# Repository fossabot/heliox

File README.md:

# Heliox

Uses: https://github.com/GHOSCHT/simple-electron-react-boilerplate

Dashboard: node-gyp fails on sqlite3 build -> set default pyhton version to python 2
```
node-gyp --python /path/to/python2.7/python.exe
```
or
```
npm config set python /path/to/executable/python2.7
```   

## License

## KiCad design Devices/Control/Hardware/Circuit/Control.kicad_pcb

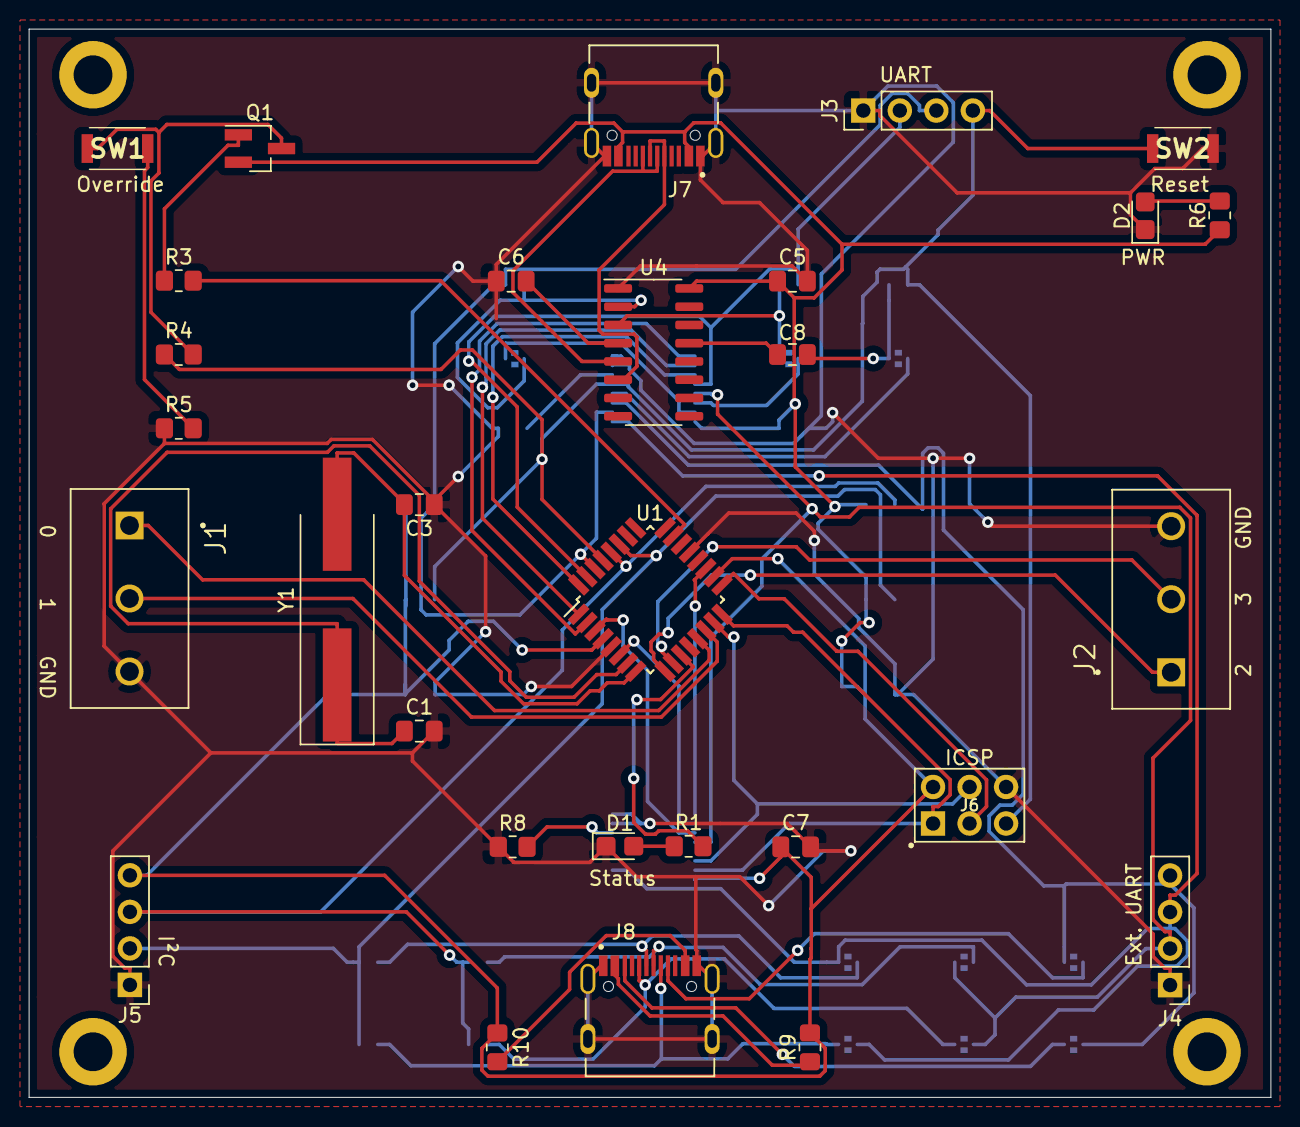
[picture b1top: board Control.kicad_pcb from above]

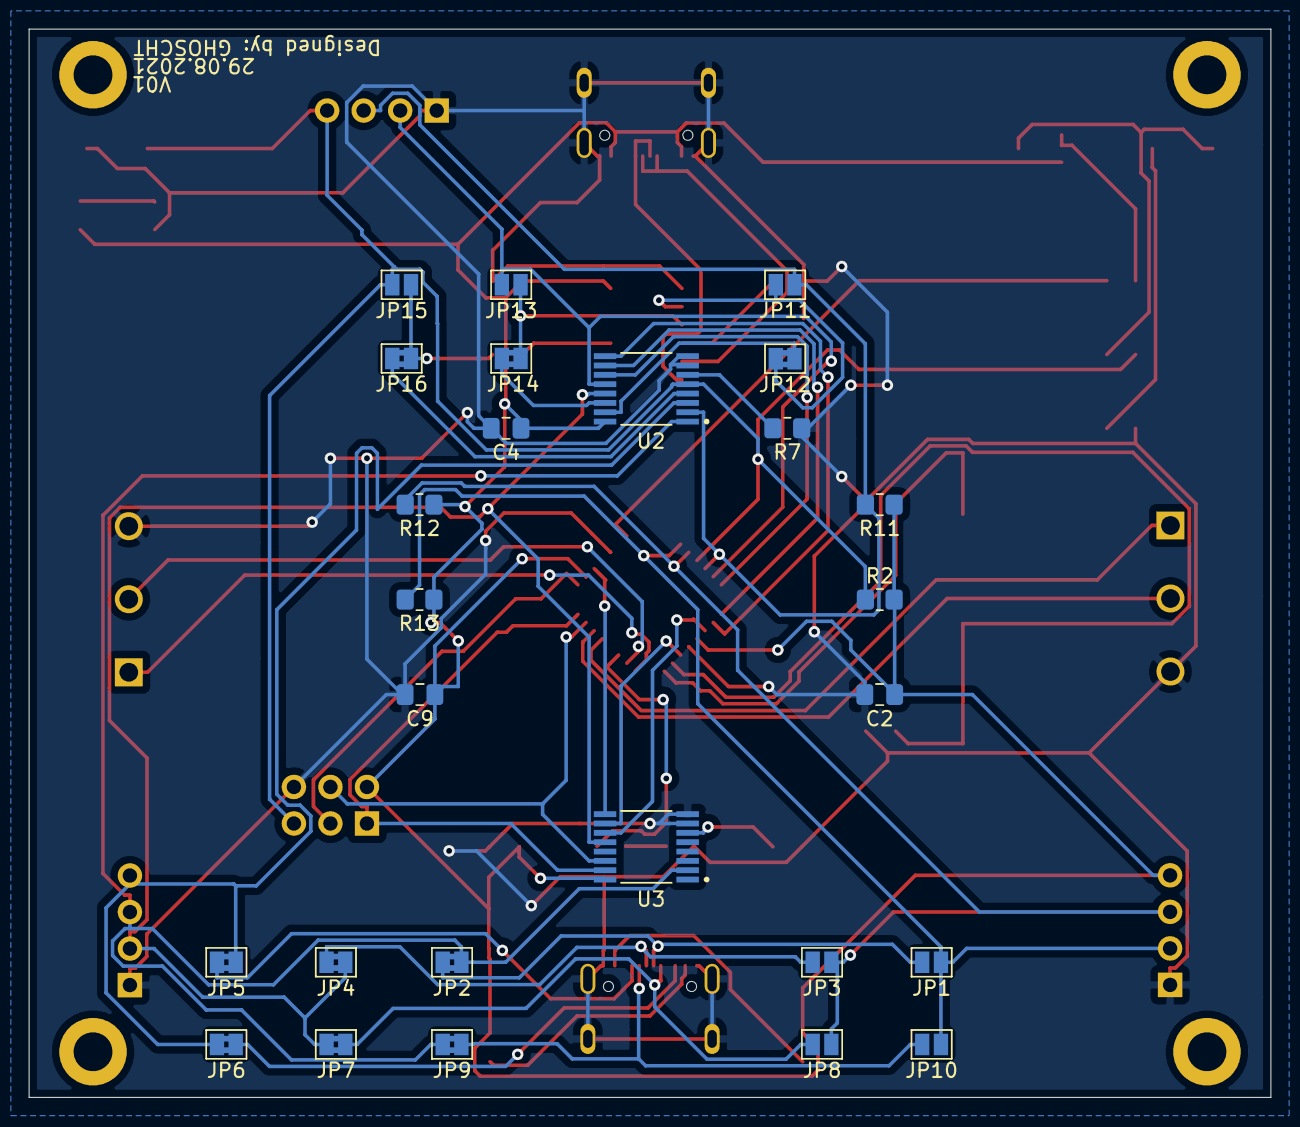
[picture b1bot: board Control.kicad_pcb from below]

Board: 2 copper layers, 86.4 x 74.3 mm, 60 parts (26 on the bottom side), 52 nets.

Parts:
C1, C3: 22p; C_0805_2012Metric_Pad1.18x1.45mm_HandSolder
C2, C4, C5, C6, C7, C8, C9: 100n; C_0805_2012Metric_Pad1.18x1.45mm_HandSolder
D1, D2: 17-21/BHC-XL2M2TY/3T; LED_0805_2012Metric_Castellated
J1, J2: Screw_Terminal_01x03; CUI_TB006-508-03BE
J3, J4, J5: Conn_01x04; PinHeader_1x04_P2.54mm_Vertical
J6: AVR-ISP-6; AVR-ISP
J7, J8: TYPE-C-31-M-12; HRO_TYPE-C-31-M-12
JP1, JP3, JP8, JP10, JP11, JP13, JP15: SolderJumper; SolderJumper-2_P1.3mm_Open_Pad1.0x1.5mm
JP2, JP4, JP5, JP6, JP7, JP9, JP12, JP14, JP16: SolderJumper_Bridged; SolderJumper-2_P1.3mm_Bridged2Bar_Pad1.0x1.5mm
MNT1, MNT2, MNT3, MNT4: MountingHole_2.7mm_M2.5_DIN965_Pad
Q1: Q_NPN_BCE; SOT-23_Handsoldering
R1, R6: 200; R_0805_2012Metric_Pad1.20x1.40mm_HandSolder
R2, R7, R8, R11, R12, R13: 10k; R_0805_2012Metric_Pad1.20x1.40mm_HandSolder
R3, R5, R9, R10: 40.2; R_0805_2012Metric_Pad1.20x1.40mm_HandSolder
R4: 120; R_0805_2012Metric_Pad1.20x1.40mm_HandSolder
SW1, SW2: SW_Push; SKRKAEE020
U1: ATmega328PB-AU; TQFP-32_7x7mm_P0.8mm
U2, U3: CD74HC4053PWR; SOP65P640X120-16N
U4: CH340C; SOIC-16_3.9x9.9mm_P1.27mm
Y1: 16MHz; Crystal_SMD_HC49-SD_HandSoldering

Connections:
D+: J7.A6, J7.B6, U4.5
D-: J7.A7, J7.B7, U4.6
EXTRST: J4.4, JP5.1, JP6.2, U2.3
EXTRX: J4.3, JP2.1, JP9.2, U2.1, U3.2
EXTTX: J4.2, JP4.1, JP7.2, U2.13, U3.12
GND: C1.2, C2.2, C3.2, C4.2, C5.2, C6.1, C7.2, C9.2, D1.1, D2.1, J1.3, J2.3, J3.1, J4.1, J5.1, J6.6, J7.A1B12, J7.B1A12, J7.S1, J7.S2, J7.S3, J7.S4, J8.A1B12, J8.B1A12, J8.S1, J8.S2, J8.S3, J8.S4, R5.1, R7.1, R8.1, SW2.2, U1.5, U1.21, U2.7, U2.8, U3.7, U3.8, U4.1
LED: R1.2, U1.11
MISO: J6.1, U1.16, U3.15
MOSI: J6.4, U1.15, U3.14
MUX1S0: U1.32, U2.11
MUX1S1: U1.1, U2.10
MUX1S2: U1.2, U2.9
MUX2S0: U1.3, U3.11
MUX2S1: U1.6, U3.10
MUX2S2: U1.19, U3.9
MUXRST: JP16.1, U2.4
MUXRX: JP12.1, U2.15
MUXTX: JP14.1, U2.14
unnamed: C6.2, U4.4
unnamed: C8.1, JP15.1, JP16.2
unnamed: C8.2, U4.13
unnamed: D1.2, R1.1
unnamed: D2.2, R6.1
unnamed: J8.A4B9, R9.2
unnamed: J8.A6, JP1.2, JP2.2
unnamed: J8.A7, JP3.2, JP4.2
unnamed: J8.A8, JP5.2
unnamed: J8.B4A9, R10.2
unnamed: J8.B6, JP9.1, JP10.2
unnamed: J8.B7, JP7.1, JP8.2
unnamed: J8.B8, JP6.1
unnamed: JP11.1, JP12.2, U4.2
unnamed: JP13.1, JP14.2, U4.3
unnamed: Q1.1, R3.1
unnamed: Q1.3, R4.2, SW1.1
unnamed: R5.2, SW1.2
unnamed: R7.2, U2.6
unnamed: R8.2, U3.6
RST: J3.4, J6.5, JP15.2, R2.1, R4.1, SW2.1, U1.29, U2.5
RX: J3.3, JP11.2, R11.2, U1.30, U2.2
SCK: J6.3, U1.17
SCL: J5.3, JP3.1, JP8.1, R12.2, U1.28
SDA: J5.2, JP1.1, JP10.1, R13.2, U1.27
SIG1A: J1.1, U1.13
SIG1B: J1.2, U1.14
SIG2A: J2.1, U1.9
SIG2B: J2.2, U1.10
STOPRST: R3.2, U1.23
TX: J3.2, JP13.2, U1.31, U2.12
VCC: C2.1, C4.1, C5.1, C7.1, C9.1, J5.4, J6.2, J7.A4B9, J7.B4A9, Q1.2, R2.2, R6.2, R9.1, R10.1, R11.1, R12.1, R13.1, U1.4, U1.18, U2.16, U3.16, U4.16
XTAL1: C1.1, U1.7, Y1.1
XTAL2: C3.1, U1.8, Y1.2

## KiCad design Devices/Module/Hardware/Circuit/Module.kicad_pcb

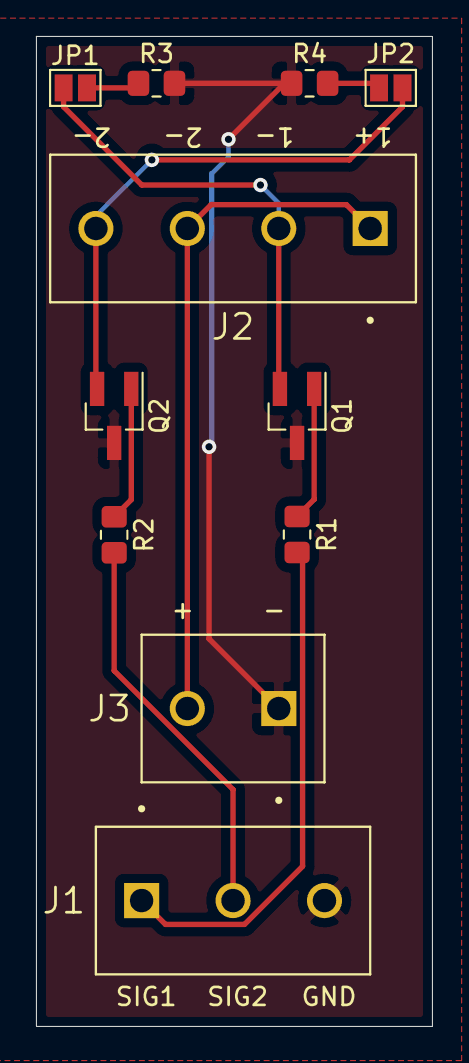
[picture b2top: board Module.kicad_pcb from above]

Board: 2 copper layers, 22.0 x 55.0 mm, 11 parts (0 on the bottom side), 10 nets.

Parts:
J1: Screw_Terminal_01x03; CUI_TB006-508-03BE
J2: Screw_Terminal_01x04; CUI_TB006-508-04BE
J3: Screw_Terminal_01x02; CUI_TB006-508-02BE
JP1, JP2: Jumper; SolderJumper-2_P1.3mm_Open_Pad1.0x1.5mm
Q1, Q2: Q_NPN_BCE; SOT-23_Handsoldering
R1, R2: 470; R_0805_2012Metric_Pad1.20x1.40mm_HandSolder
R3, R4: 10k; R_0805_2012Metric_Pad1.20x1.40mm_HandSolder

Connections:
GND: J1.3, J3.1, Q1.3, Q2.3, R3.2, R4.1
LED1N: J2.2, JP1.1, Q1.2
LED2N: J2.4, JP2.1, Q2.2
unnamed: JP1.2, R3.1
unnamed: JP2.2, R4.2
unnamed: Q1.1, R1.1
unnamed: Q2.1, R2.1
SIG1: J1.1, R1.2
SIG2: J1.2, R2.2
VCC: J2.1, J2.3, J3.2

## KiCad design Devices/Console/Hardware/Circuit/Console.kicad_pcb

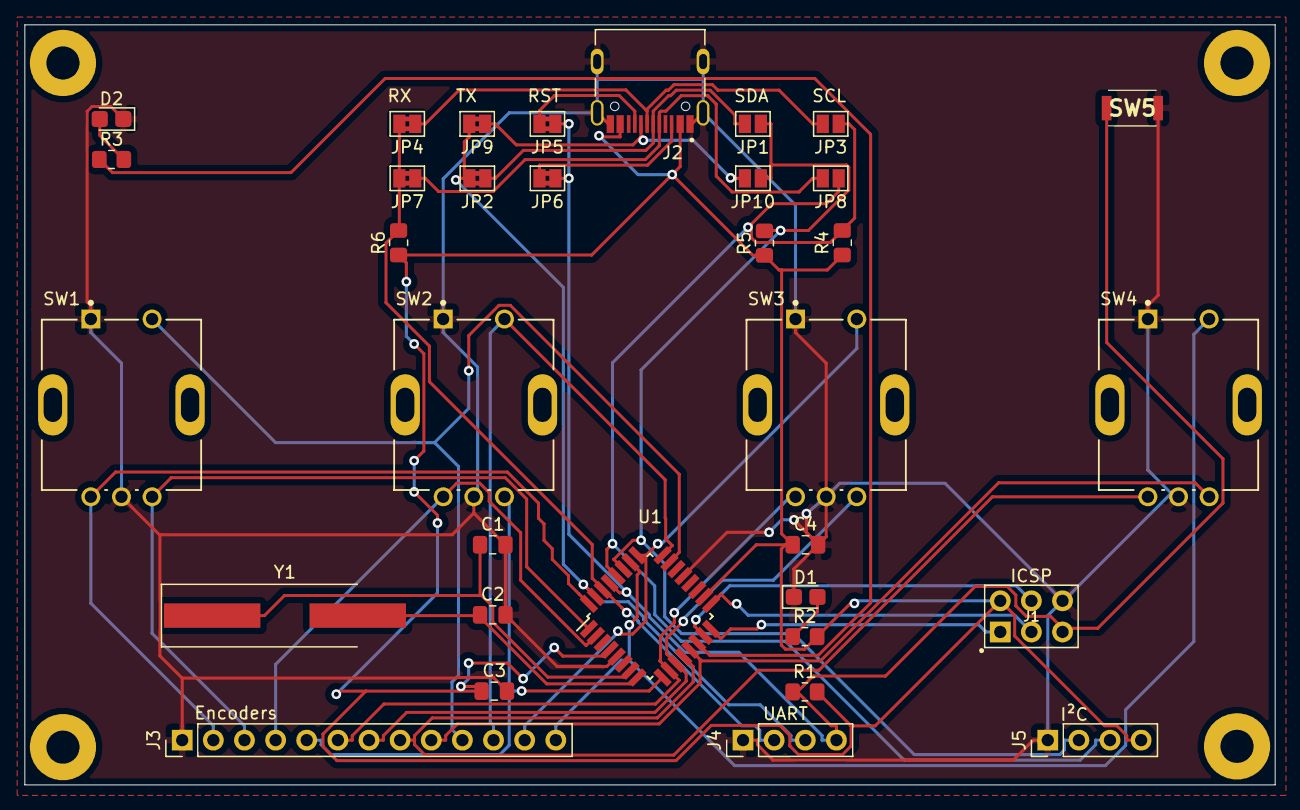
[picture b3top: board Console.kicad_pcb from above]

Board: 2 copper layers, 102.0 x 62.0 mm, 38 parts (0 on the bottom side), 33 nets.

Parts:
C1, C2: 22p; C_0805_2012Metric_Pad1.18x1.45mm_HandSolder
C3, C4: 100n; C_0805_2012Metric_Pad1.18x1.45mm_HandSolder
D1, D2: 17-21/BHC-XL2M2TY/3T; LED_0805_2012Metric_Castellated
J1: AVR-ISP-6; AVR-ISP
J2: TYPE-C-31-M-12; HRO_TYPE-C-31-M-12
J3: Conn_01x13; PinHeader_1x13_P2.54mm_Vertical
J4, J5: Conn_01x04; PinHeader_1x04_P2.54mm_Vertical
JP1, JP3, JP8, JP10: SolderJumper; SolderJumper-2_P1.3mm_Open_Pad1.0x1.5mm
JP2, JP4, JP5, JP6, JP7, JP9: SolderJumper_Bridged; SolderJumper-2_P1.3mm_Bridged2Bar_Pad1.0x1.5mm
PAD1, PAD2, PAD3, PAD4: MountingHole_2.7mm_M2.5_Pad
R1, R4, R5, R6: 10k; R_0805_2012Metric_Pad1.20x1.40mm_HandSolder
R2, R3: 200; R_0805_2012Metric_Pad1.20x1.40mm_HandSolder
SW1, SW2, SW3, SW4: PEC11R-4220F-S0012; Bourns-PEC11R-4220F-S0012-MFG
SW5: SW_Push; SKRKAEE020
U1: ATmega328PB-AU; TQFP-32_7x7mm_P0.8mm
Y1: 16MHz; Crystal_SMD_HC49-SD_HandSoldering

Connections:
BTN1: J3.10, SW1.S2, U1.23
BTN2: J3.11, SW2.S2, U1.24
BTN3: J3.12, SW3.S2, U1.25
BTN4: J3.13, SW4.S2, U1.26
ENC1A: J3.2, SW1.A, U1.32
ENC1B: J3.3, SW1.B, U1.1
ENC2A: J3.4, SW2.A, U1.2
ENC2B: J3.5, SW2.B, U1.9
ENC3A: J3.6, SW3.A, U1.10
ENC3B: J3.7, SW3.B, U1.11
ENC4A: J3.8, SW4.A, U1.12
ENC4B: J3.9, SW4.B, U1.13
GND: C1.2, C2.2, C3.2, C4.2, D1.1, D2.1, J1.6, J2.A1B12, J2.B1A12, J2.S1, J2.S2, J2.S3, J2.S4, J3.1, J4.1, J5.1, SW1.C, SW1.S1, SW2.C, SW2.S1, SW3.C, SW3.S1, SW4.C, SW4.S1, SW5.2, U1.5, U1.21
LED: R3.2, U1.14
MISO: J1.1, U1.16
MOSI: J1.4, U1.15
unnamed: D1.2, R2.1
unnamed: D2.2, R3.1
unnamed: J2.A6, JP1.2, JP2.2
unnamed: J2.A7, JP3.2, JP4.2
unnamed: J2.A8, JP5.2
unnamed: J2.B6, JP9.1, JP10.1
unnamed: J2.B7, JP7.1, JP8.1
unnamed: J2.B8, JP6.1
RST: J1.5, J4.4, JP5.1, JP6.2, R1.1, SW5.1, U1.29
RX: J4.2, JP4.1, JP7.2, R6.2, U1.30
SCK: J1.3, U1.17
SCL: J5.3, JP3.1, JP8.2, R4.2, U1.28
SDA: J5.2, JP1.1, JP10.2, R5.2, U1.27
TX: J4.3, JP2.1, JP9.2, U1.31
VCC: C3.1, C4.1, J1.2, J2.A4B9, J2.B4A9, J5.4, R1.2, R2.2, R4.1, R5.1, R6.1, U1.4, U1.18
XTAL1: C1.1, U1.7, Y1.1
XTAL2: C2.1, U1.8, Y1.2

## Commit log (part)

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2020-07-28 Add Dashboard
2020-07-28 Create LICENSE
2020-07-30 Switch electron boilerplates
2020-07-30 Add on & off commands + Relay state communication
2020-07-30 Add serialport package
2020-07-30 remove menu bar
2020-07-30 first serial com test
2020-08-01 Remove default content
2020-08-01 Add redux store
2020-08-01 Add material ui
2020-08-01 First test of serial control
2020-08-01 Add darkmode
2020-08-01 Change app name
2020-08-01 Add icon, size & name change
2020-08-01 Remove test component
2020-08-01 Add conditional styling
2020-08-01 Remove unnecessary props
2020-08-01 Add hide to tray
2020-08-01 Change icon
2020-08-01 Simplify tray creation
2020-08-01 cleanup
2020-08-01 Add icon to resources
2020-08-01 Add new styling
2020-08-01 No logical changes, only clarification
2020-08-01 Change file format of icon
2020-08-01 Bump mixin-deep from 1.3.1 to 1.3.2 in /Dashboard
    Bumps [mixin-deep](https://github.com/jonschlinkert/mixin-deep) from 1.3.1 to 1.3.2.
    - [Release notes](https://github.com/jonschlinkert/mixin-deep/releases)
    - [Commits](https://github.com/jonschlinkert/mixin-deep/compare/1.3.1...1.3.2)
2020-08-01 Bump electron from 8.2.2 to 8.2.4 in /Dashboard
    Bumps [electron](https://github.com/electron/electron) from 8.2.2 to 8.2.4.
    - [Release notes](https://github.com/electron/electron/releases)
    - [Changelog](https://github.com/electron/electron/blob/master/docs/breaking-changes.md)
    - [Commits](https://github.com/electron/electron/compare/v8.2.2...v8.2.4)
2020-08-01 Bump lodash from 4.17.11 to 4.17.19 in /Dashboard
    Bumps [lodash](https://github.com/lodash/lodash) from 4.17.11 to 4.17.19.
    - [Release notes](https://github.com/lodash/lodash/releases)
    - [Commits](https://github.com/lodash/lodash/compare/4.17.11...4.17.19)
2020-08-02 Disable publishing
2020-08-02 Arduino builder error test
2020-08-02 Revert "Arduino builder error test"
    This reverts commit 97cf7e37e65544a997c7bfe0c96db386e0ee02a5.
2020-08-02 Icon experimentation
2020-08-02 Linting changes
2020-08-05 Add single instance lock
2020-08-07 Hardware config changes
2020-08-07 Comments + minor changes
2020-08-07 Remove quit event
2020-08-07 take trayIcon oncklick event out of creation function
2020-08-07 More comments
2020-08-07 Remove icon2.ico
2020-08-07 Remove unused variable
2020-08-07 Remove winow focussing
2020-08-07 Add devtools shortcut
2020-08-07 Display tray icon only after window content completely loaded
2020-08-08 Fix memory leak
2020-08-08 Renaming
2020-08-08 Change app icon
2020-08-08 Add custom installation path to installer
2020-08-08 Change installer name
2020-08-08 Add app preferences to constants file
2020-08-10 Add status header
2020-08-10 Add connection reducer
2020-12-18 Switch to PWM instead of Digital bjt control
2020-12-19 Implement PWM dimming via COM
2020-12-27 Transfer Code to PIO
2020-12-27 Start Console firmware
2020-12-27 Implemented button sending over i2c
2020-12-31 Got the control software working now pog
2021-01-01 Changed strings to cstrings
2021-01-01 Add one rotary encoder
2021-03-27 Add Button Debouncing
2021-06-28 idk what i did there -> just for backup purposes
2021-06-28 Change COM Ports
2021-06-28 Add support for multiple encoders
2021-06-29 Add selfmade electron/react boilerplate
2021-06-29 Move electron to dev dependencies
2021-06-30 Add husky
2021-06-30 Fix eslint errors
2021-06-30 Add husky on commit lint
2021-06-30 Add console exception
2021-06-30 Finalize on commit lint
2021-06-30 Remove crap erb try
2021-06-30 Fix typescript config error "Cannot write file 'electron.js' because it would overwrite input file.
2021-06-30 Add serial port listing test
2021-06-30 Implement Build Workflows
2021-06-30 bump webpack-dev-server from 3.11.0 to 4.0.0-beta.3
2021-06-30 Revert "bump webpack-dev-server from 3.11.0 to 4.0.0-beta.3"
    This reverts commit 663816cbc510d18714eb515c26fb14aa73c98917.
2021-06-30 Add acrylic background
2021-06-30 Embed window border style into html
2021-06-30 Revert "Update Electron.yml"
    This reverts commit d75f434b5d17c34ee545fd15fcde12c8cb2be1e5.
2021-06-30 Rename electron window
2021-06-30 Transfer electron settings from previous dashboard version
2021-06-30 Add proper tray icon image
2021-06-30 Add proper program icons
2021-06-30 Customize installer
2021-06-30 Only hide window onblur when in production
2021-07-09 First knob design
2021-07-09 Add svg support
2021-07-09 Change window border color to match windows
2021-07-09 Update Knob source file
2021-07-09 Add knob to project
2021-07-09 Revert "Change window border color to match windows"
    This reverts commit a5d60de5a249751459dbf74368af299901a462b5.
2021-07-10 Put status text into seperate group
2021-07-10 First rough implementation of knob
2021-07-10 Asset folder cleanup
2021-07-10 [ImgBot] Optimize images
    *Total -- 159.52kb -> 146.06kb (8.44%)
    /Dashboard/assets/icons/png/256x256.png -- 12.21kb -> 9.52kb (21.99%)
    /Dashboard/assets/icons/png/512x512.png -- 25.85kb -> 20.27kb (21.59%)
    /Dashboard/assets/icons/png/128x128.png -- 5.98kb -> 4.78kb (20.01%)
    /Dashboard/assets/knob/Knob.svg -- 1.56kb -> 1.34kb (13.75%)
    /Dashboard/assets/icons/png/64x64.png -- 2.80kb -> 2.45kb (12.43%)
2021-07-10 Implement knob rotation
2021-07-10 Implement knob function triggering
2021-07-10 Change step amount for action to trigger
2021-07-10 Implement rough attempt at dynamic win10 color scheme
2021-07-10 Use styled-components for window border
2021-07-10 Add testing COM connection to knob
2021-08-04 Bump tar from 4.4.13 to 4.4.15 in /Dashboard
    Bumps [tar](https://github.com/npm/node-tar) from 4.4.13 to 4.4.15.
    - [Release notes](https://github.com/npm/node-tar/releases)
    - [Changelog](https://github.com/npm/node-tar/blob/main/CHANGELOG.md)
    - [Commits](https://github.com/npm/node-tar/compare/v4.4.13...v4.4.15)
    ---
    updated-dependencies:
2021-08-05 File restructuring
2021-08-05 Adapt pio build action to file restructuring
2021-08-10 Add KiCad gitignore
2021-08-10 Rough console part selection
2021-08-10 Exchange Micro USB with Type C
2021-08-10 First rough console schematic
2021-08-10 Add encoder breakout connector
2021-08-10 Add communication breakout pins
2021-08-10 Add schematic annotations
2021-08-11 Add led power indicator
2021-08-11 Add ERC power flag
2021-08-13 Bump path-parse from 1.0.6 to 1.0.7 in /_Dashboard
    Bumps [path-parse](https://github.com/jbgutierrez/path-parse) from 1.0.6 to 1.0.7.
    - [Release notes](https://github.com/jbgutierrez/path-parse/releases)
    - [Commits](https://github.com/jbgutierrez/path-parse/commits/v1.0.7)
    ---
    updated-dependencies:
    - dependency-name: path-parse
2021-08-13 Add basic component selection to control
2021-08-13 Make serial solder jumper bridged
2021-08-13 Add first USB to serial functionality
2021-08-15 Add uart multiplexer
2021-08-15 Add console UART muxing
2021-08-15 Add control reset functionality
2021-08-15 Add reset button to console
2021-08-15 Change console reset button symbol + solder jumper footprint
2021-08-15 Add external reset sensing to control
2021-08-16 Add first rough connections of atmega328pb
2021-08-17 Restructure control schematic
2021-08-17 Add status led to control
2021-08-17 Add PB processor & status led to console
2021-08-17 Add module circuit files
2021-08-17 Add module enclosure files
2021-08-17 Bump jszip from 3.6.0 to 3.7.1 in /Dashboard
    Bumps [jszip](https://github.com/Stuk/jszip) from 3.6.0 to 3.7.1.
    - [Release notes](https://github.com/Stuk/jszip/releases)
    - [Changelog](https://github.com/Stuk/jszip/blob/master/CHANGES.md)
    - [Commits](https://github.com/Stuk/jszip/compare/v3.6.0...v3.7.1)
    ---
    updated-dependencies:
2021-08-17 Bump url-parse from 1.5.1 to 1.5.3 in /Dashboard
    Bumps [url-parse](https://github.com/unshiftio/url-parse) from 1.5.1 to 1.5.3.
    - [Release notes](https://github.com/unshiftio/url-parse/releases)
    - [Commits](https://github.com/unshiftio/url-parse/compare/1.5.1...1.5.3)
    ---
    updated-dependencies:
    - dependency-name: url-parse
2021-08-17 Add 1x06 screw terminal files to control
2021-08-17 Add module circuit
2021-08-19 Add input serial mux & Change pin header footprint
2021-08-19 Change pin header size
2021-08-19 Finish module PCB layout
2021-08-19 First console PCB layout
2021-08-19 Change ISP footprint to through-hole
2021-08-19 Relocate ISP header
2021-08-19 Flip components for easier wiring
2021-08-19 Add second more centered pcb layout
2021-08-19 Finalize PCB
2021-08-19 Add breakout pin description
2021-08-19 Add proper mounting holes
2021-08-19 Improve routing with freerouting + manual fixes
2021-08-19 Add additional decoupling capacitor
2021-08-19 Switch LED location
2021-08-19 Add pulldown resistor
2021-08-23 Change pulldown track width
2021-08-23 Bigger spacing between encoders
2021-08-23 Wider encoder gap pcb traces
2021-08-23 Plot Gerber files
2021-08-23 Switch to Minicore bootloader
2021-08-23 Switch console to Minicore
2021-08-23 Test build without specified environment
2021-08-24 Switch to Minicore & enable reset toggle on upload
2021-08-24 Add UART upload forwarding
2021-08-25 Generate Gerbers
2021-08-25 Add reset hardware override
2021-08-25 Fix git destroying line ending after discarding changes
2021-08-25 Probably fix knob skipping steps if devtools closed
2021-08-26 Implement light status feedback
2021-08-26 Remove old backup dashboard
2021-08-26 Bump webpack-dev-server from 3.1.0 to 4.0.0
2021-08-26 Add Figma mockup link
2021-08-26 Buffer boundary check - test 1
2021-08-26 Revert "Buffer boundary check - test 1"
    This reverts commit 1c0c7449838e07e96a0cbd041e050235f85f8ebe.
2021-08-26 Platformio will now be recommended
2021-08-26 First Redux implementation
2021-08-26 Remove Gerber folder
2021-08-26 Exclude Gerber folder from sync
2021-08-27 Add node-gyp notice
2021-08-27 First implementation of redux connection system
2021-08-27 Serial Port can now be set in-app
2021-08-27 Chalk moved from dev dependencies to real deps
2021-08-27 Switch from abandonned remote-dev-server to @redux-devtools/cli
2021-08-27 Rename PortManager file
2021-08-27 Add serial disconnect event
2021-08-27 Fix exception when disconnecting
2021-08-27 Scale displayed status
2021-08-27 Pin dependencies
2021-08-28 Update actions/setup-node action to v2
2021-08-28 Update dependency @types/jest to v27
2021-08-28 Update dependency husky to v7
2021-08-28 Update dependency style-loader to v3
2021-08-28 Update react monorepo to v17
2021-08-28 Update dependency fs-extra to v10
2021-08-28 Deleted as now unnecessary
2021-08-28 Update dependency html-webpack-plugin to v5
2021-08-28 Revert "Deleted as now unnecessary"
    This reverts commit f05d1ca368186573c3b0d0502994c2e5eff0c111.
2021-08-28 Update dependency css-loader to v6
2021-08-28 Prepare v2.0.0 Release
2021-08-29 Add UART/I2C pull-up resistors
2021-08-29 Add port names on silkscreen
2021-08-29 First control PCB
2021-08-29 Add mounting holes & component description
2021-08-29 Add version number & author information
2021-08-29 Fix output port numbering
2021-08-30 Update dependency electron to v14
2021-09-09 Update babel monorepo
2021-09-12 Revert "Merge pull request #33 from GHOSCHT/renovate/electron-14.x"
    This reverts commit bfd14058efe47fe43db0f4ce44d17d9534d087e9, reversing
    changes made to 70a1624701290843d28c8e07d527cdf19748c332.
2021-09-24 Update dependency react-select to v5
2021-10-01 Update dependency @types/react-select to v5
2021-10-28 Fix autoformat interfering with eslint
2021-10-28 Implement adaptive taskbar size
2021-10-28 First visual addition of missing knobs
2021-10-28 Add functionality to all knobs
2021-10-28 Prepare new version release
2021-10-28 Persist selected serial port
2021-10-28 Fix serial port persistence
2021-10-28 Fix overwriting of blacklisted elements when refreshing
2021-12-31 First switch to redux-toolkit
2021-12-31 Transform reducers to slices
2021-12-31 Remove unnecessary code
2021-12-31 Switch to integrated redux devtools
2021-12-31 Comment out currently unused code
2021-12-31 Simplify class usage
2021-12-31 First implementation of connection in middleware
2021-12-31 Hook up interface to serial connection
2021-12-31 Hook up disconnect to UI button
2021-12-31 Readd complex connection logic
2022-01-01 Add initial state to message
2022-01-01 Add serial communication demo
2022-01-07 Fix electron not starting due to "port overlap"
